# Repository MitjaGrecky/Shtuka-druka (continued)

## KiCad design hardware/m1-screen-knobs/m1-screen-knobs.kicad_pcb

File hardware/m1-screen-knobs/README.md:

# M1 - screen knobs module

**Current source (R148, 14.11.2026): rev 0.5** - four TI LP5864 (one per pair of rings), 12 RGB LEDs per ring, 4 corner holes + 3 in the gaps (x 56, 112, 168 mm, P97), 163 parts. `gen/design.py` builds rev 0.5 by default; `M1_LP=0` builds the old rev 0.3 (two IS31FL3741A, 13 LEDs, 8 holes), kept for history. The KiCad files here and `hardware/for-routing/M1` agree. The text below describes rev 0.1–0.3 (history).

Eight smooth encoders with push and touch (Param 1-8 under the screen), each with a ring of 13 RGB LEDs.
Spec and reasoning: `docs/ru/30_m1_screen_knobs.md`. History (rev 0.1): schematic done, board routed except 4 connections around U1; light guide (`mech/m1_light_guide.stl`) ready to print.

| | |
|---|---|
| Board | 224 x 34 mm, 4 layers; panel position x 108.75-332.75, y 263-297 (knob row y 277, panel fold y 300) |
| Top side | 8 x Alps EC11E (smooth, switch), 104 x XINGLIGHT XL-1615RGBC-RF (LCSC C965840) |
| Bottom side | IS31FL3741A LED driver (C2940604), CY8CMBR3108 touch (C462528), 3 x 74HC165, passives, J1 |
| Bus J1 | 2 x 7, 1.27 mm: +5V x2, +3V3, GND x4, SDA, SCL, INT, SR_LOAD, SR_CLK, SR_OUT, SR_IN |
| I2C | LED driver 0x30 (ADDR=GND, R3; 0x31-0x33 via R4-R6), touch 0x37 |
| LED matrix | LED n = 13 (ring-1) + (dot-1): SW = n mod 9 + 1, CS = 3 (n div 9) + 1..3 (R, G, B); CS37-39 unused |
| Shift chain | host reads U3 D7..D0, U4, U5: E1 A, E1 B, E1 push, E2 A, ... E8 push |

## Files

- `m1-screen-knobs.kicad_pro/.kicad_sch/.kicad_pcb` - open in KiCad 10 (written in the KiCad 7 format; KiCad 10 upgrades on save).
- `mech/m1_light_guide.stl` - the light guide (R126), black PETG/PLA, 0.2 mm layers.
- `lib/` - project symbols (IS31FL3741A, XL-1615RGBC-RF, encoder with touch pin) and footprints (LED 1615, QFN-60).
- `gen/` - the generators. Edit `design.py`, then run:

```
python3 gen/make_lib.py     # symbols and footprints
python3 gen/make_sch.py     # schematic
python3 gen/make_pcb.py     # board: placement, nets, GND planes (needs KiCad's pcbnew module)
python3 gen/make_pcb.py --route freerouting-1.9.0.jar --passes 16 --finish   # + autorouting (xvfb-run, Java)
python3 gen/make_pcb.py --ses gen/last_route.ses --finish                     # rebuild from the last routing
python3 gen/make_light_guide.py mech             # light guide STL (needs bpy)
```

`UNROUTED` marks the board as not routed yet: CI keeps the DRC report but does not fail.
`QUILTER.md` - rules for handing the board to an external layout service; the parts fixed by the panel are locked.

License: CERN-OHL-S-2.0 (hardware), AGPL-3.0-or-later (scripts).

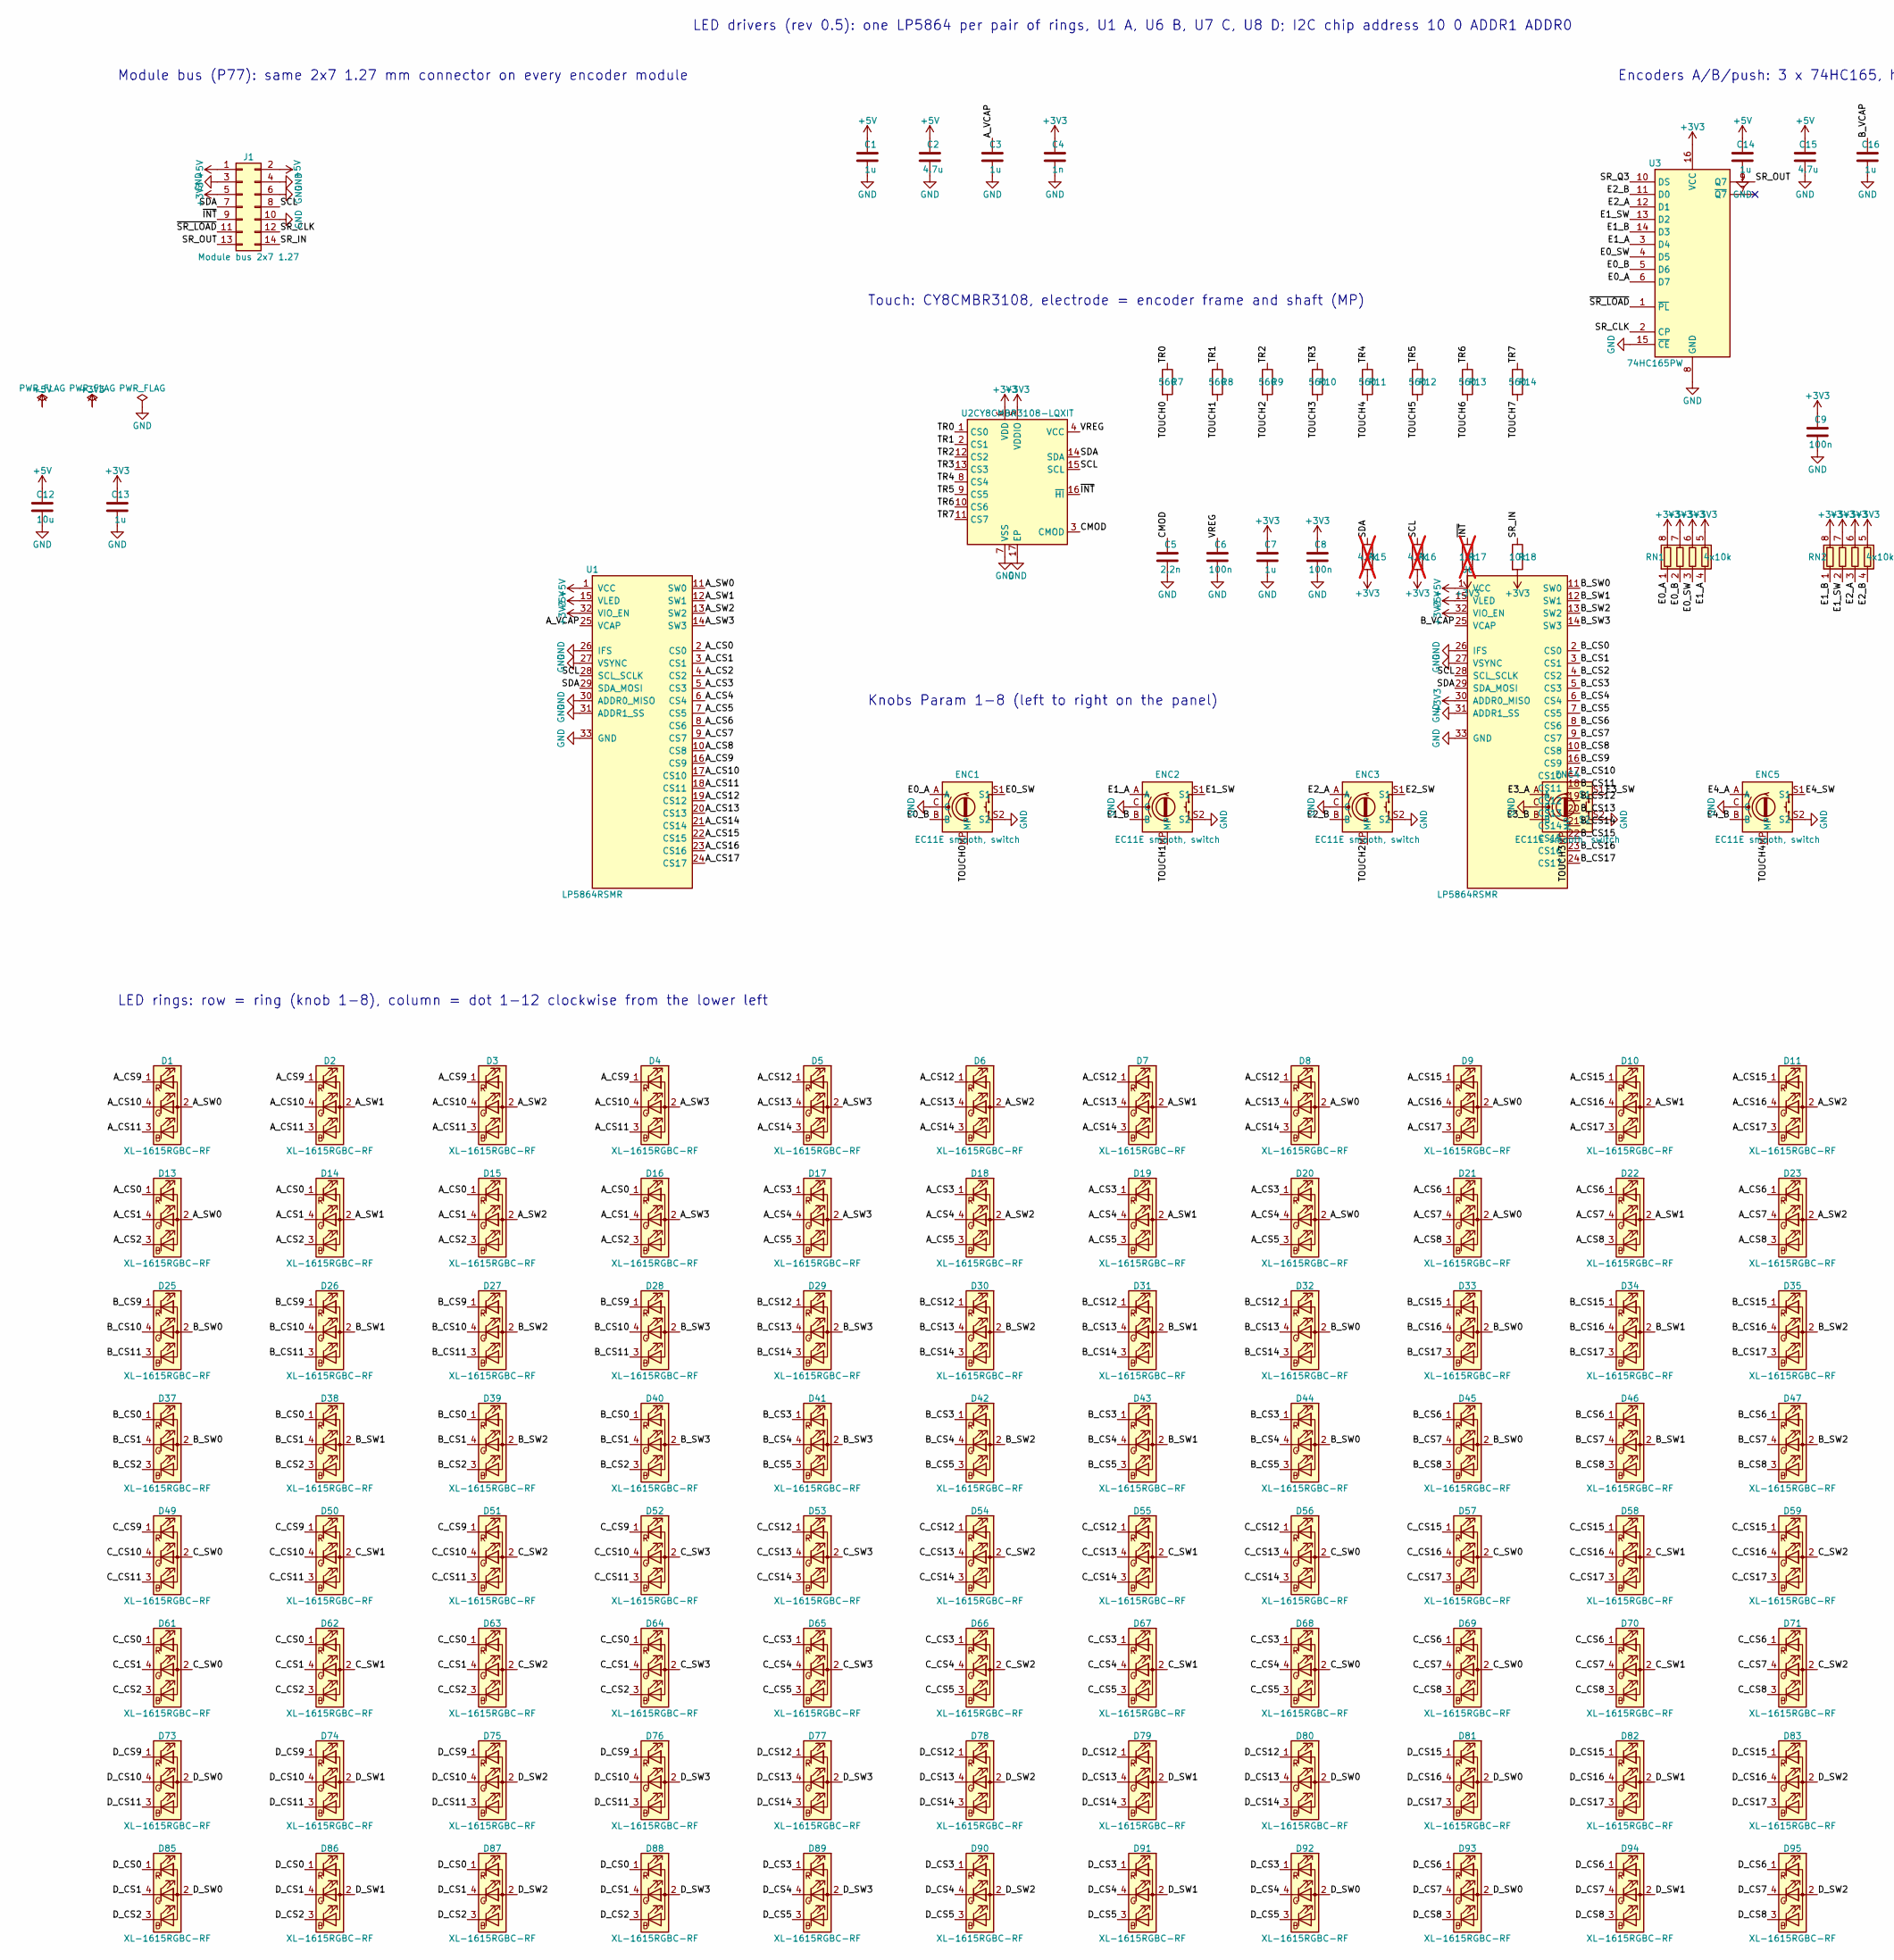
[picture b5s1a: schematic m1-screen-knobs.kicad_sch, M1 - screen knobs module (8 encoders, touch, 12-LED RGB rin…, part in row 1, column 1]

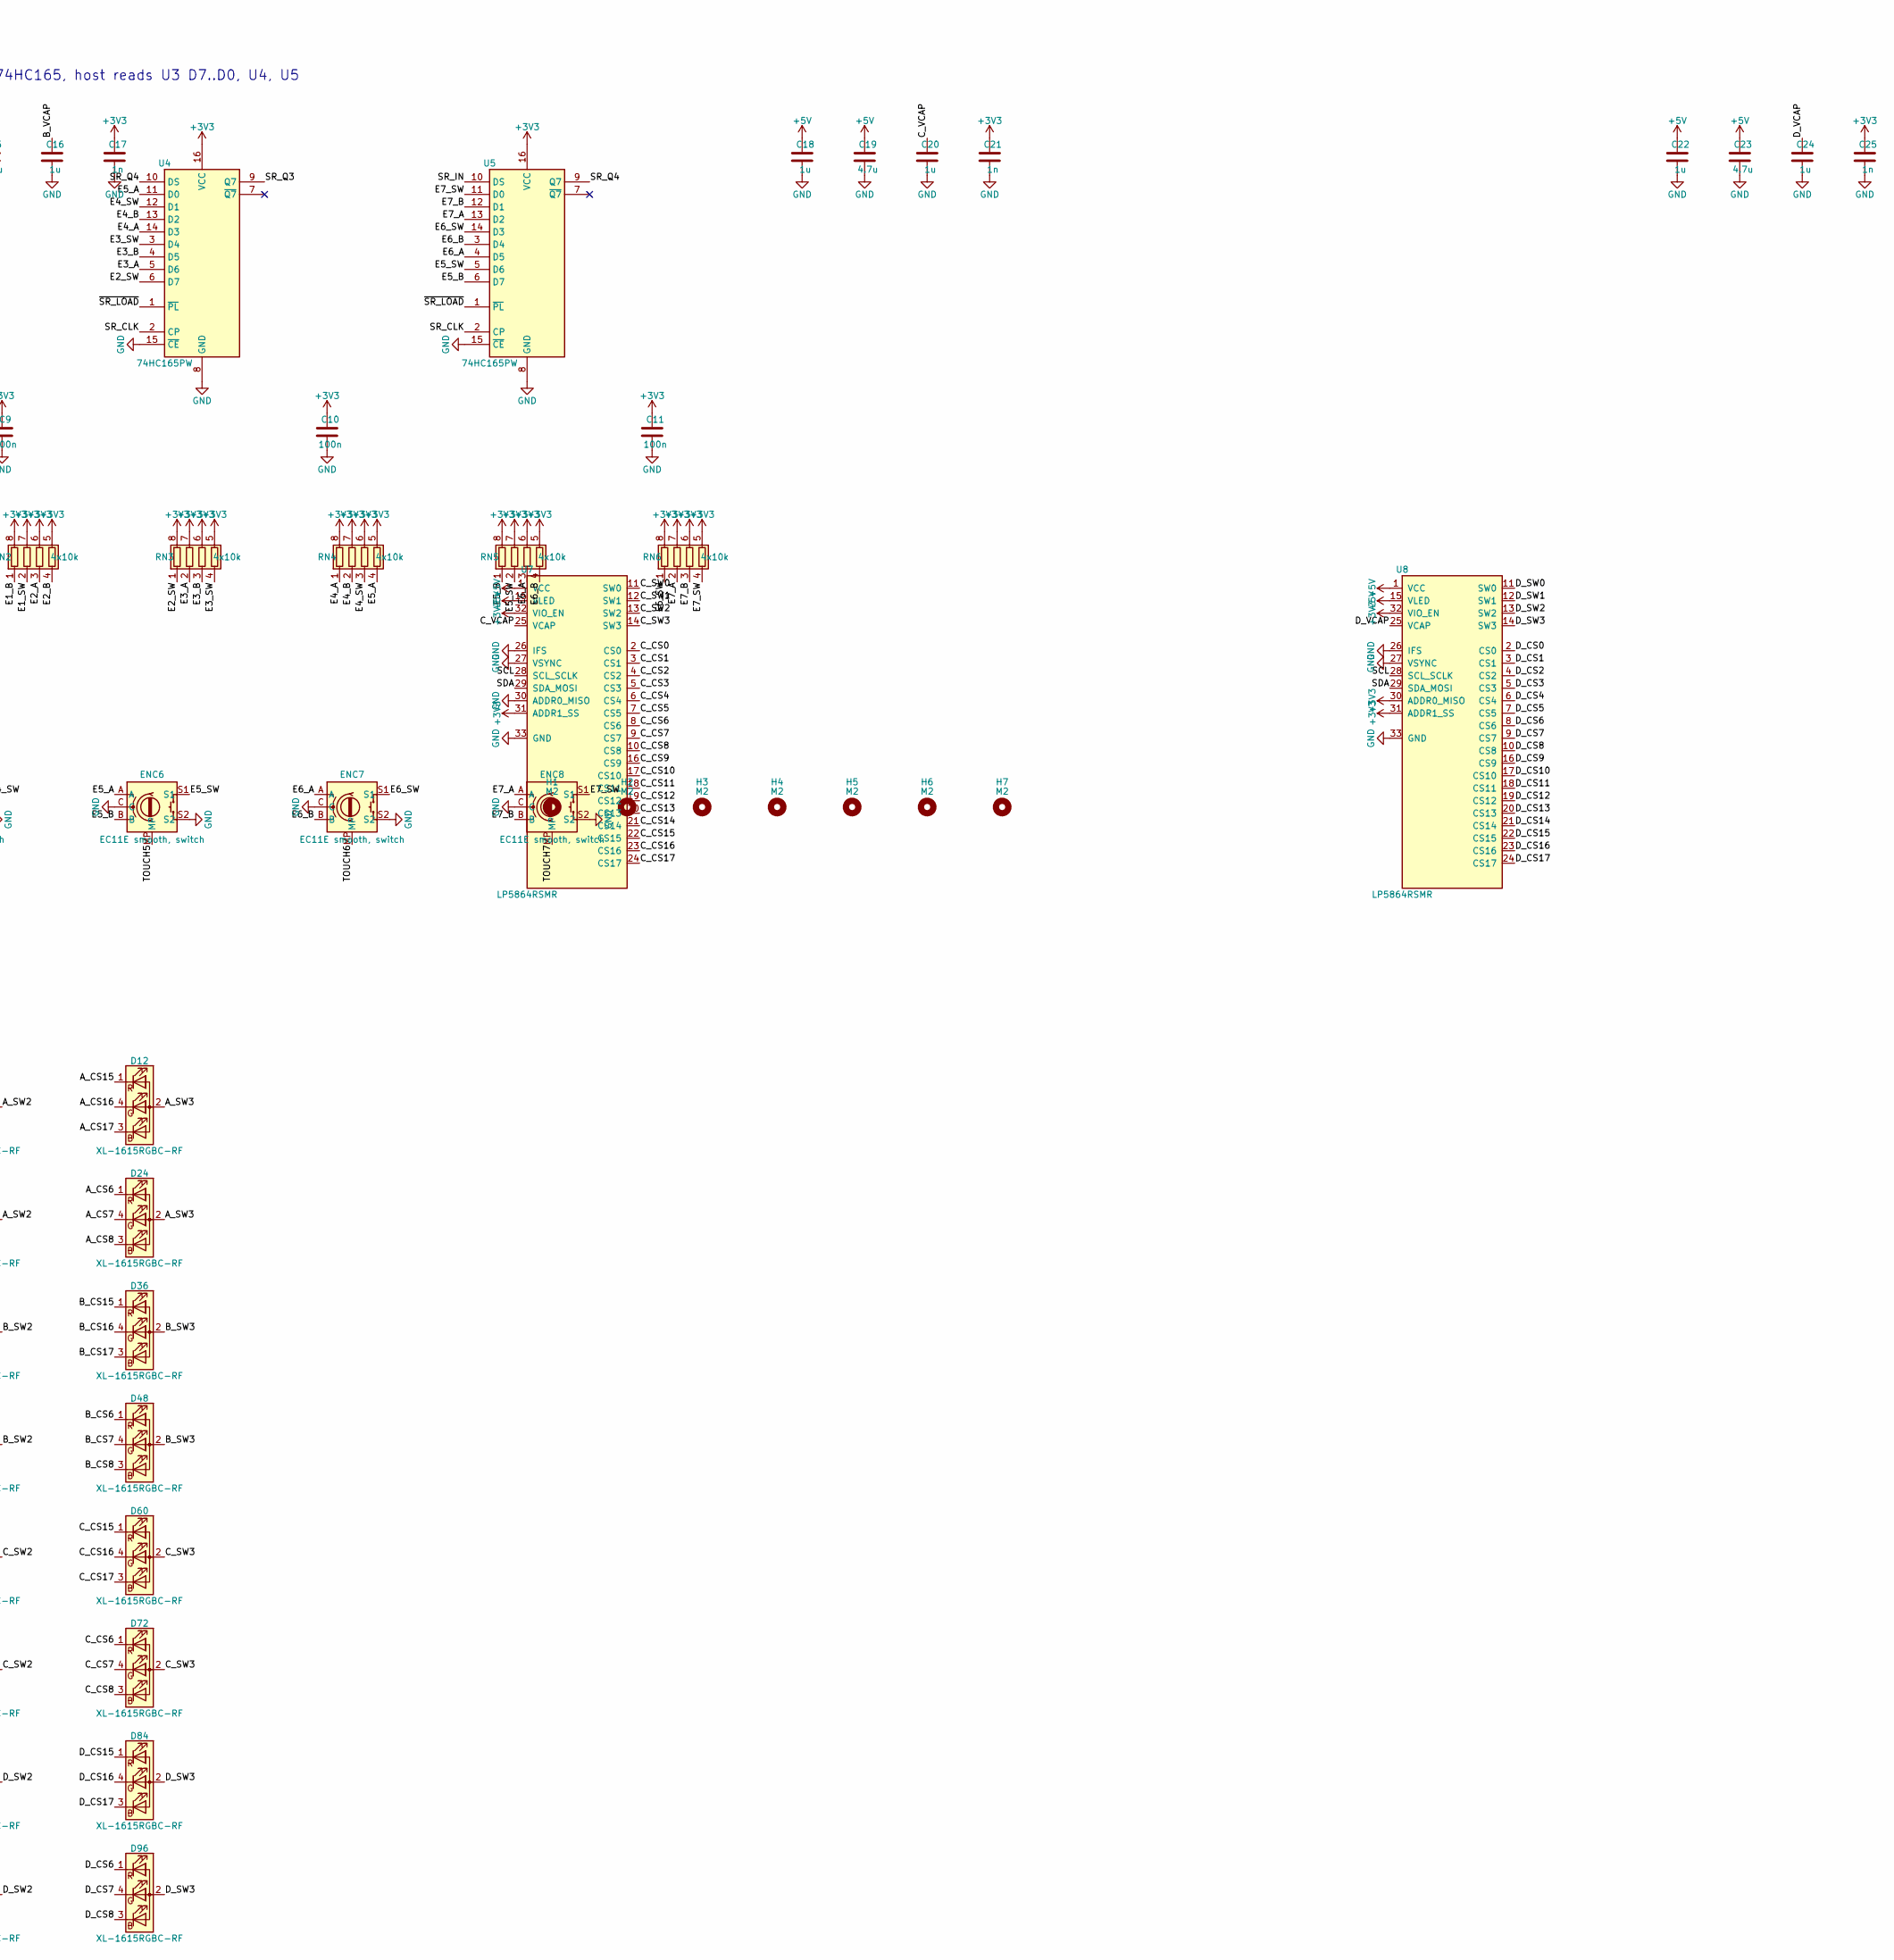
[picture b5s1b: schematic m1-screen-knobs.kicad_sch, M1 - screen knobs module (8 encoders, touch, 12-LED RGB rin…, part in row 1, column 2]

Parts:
C1, C3, C7, C13, C14, C16, C18, C20, C22, C24: 1u; C_0402_1005Metric
C2, C15, C19, C23: 4.7u; C_0805_2012Metric
C4, C17, C21, C25: 1n; C_0402_1005Metric
C5: 2.2n; C_0402_1005Metric
C6, C8, C9, C10, C11: 100n; C_0402_1005Metric
C12: 10u; C_0805_2012Metric
D1, D2, D3, D4, D5, D6, D7, D8, D9, D10, D11, D12, D13, D14, D15, D16, D17, D18, D19, D20, D21, D22, D23, D24, D25, D26, D27, D28, D29, D30, D31, D32, D33, D34, D35, D36, D37, D38, D39, D40, D41, D42, D43, D44, D45, D46, D47, D48, D49, D50, D51, D52, D53, D54, D55, D56, D57, D58, D59, D60, D61, D62, D63, D64, D65, D66, D67, D68, D69, D70, D71, D72, D73, D74, D75, D76, D77, D78, D79, D80, D81, D82, D83, D84, D85, D86, D87, D88, D89, D90, D91, D92, D93, D94, D95, D96: XL-1615RGBC-RF; LED_RGB_XL-1615RGBC_1.6x1.5mm; LCSC C965840
ENC1, ENC2, ENC3, ENC4, ENC5, ENC6, ENC7, ENC8: EC11E smooth, switch; RotaryEncoder_Alps_EC11E-Switch_Vertical_H20mm_Ring
H1, H2, H3, H4, H5, H6, H7: M2; MountingHole_2.2mm_M2
J1: Module bus 2x7 1.27; PinHeader_2x07_P1.27mm_Horizontal; LCSC C22438113
R7, R8, R9, R10, R11, R12, R13, R14: 560; R_0402_1005Metric
R15, R16: 4.7k; R_0402_1005Metric; not fitted
R17: 10k; R_0402_1005Metric; not fitted
R18: 10k; R_0402_1005Metric
RN1, RN2, RN3, RN4, RN5, RN6: 4x10k; R_Array_Convex_4x0402
U1, U6, U7, U8: LP5864RSMR; VQFN-32-1EP_4x4mm_P0.4mm_EP2.8x2.8mm; LCSC C5220564
U2: CY8CMBR3108-LQXIT; QFN-16-1EP_3x3mm_P0.5mm_EP1.7x1.7mm; LCSC C462528
U3, U4, U5: 74HC165PW; TSSOP-16_4.4x5mm_P0.65mm

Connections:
+3V3: C4.1, C7.1, C8.1, C9.1, C10.1, C11.1, C13.1, C17.1, C21.1, C25.1, J1.5, R15.2, R16.2, R17.2, R18.2, RN1.5 (R4.2), RN1.6 (R3.2), RN1.7 (R2.2), RN1.8 (R1.2), RN2.5 (R4.2), RN2.6 (R3.2), RN2.7 (R2.2), RN2.8 (R1.2), RN3.5 (R4.2), RN3.6 (R3.2), RN3.7 (R2.2), RN3.8 (R1.2), RN4.5 (R4.2), RN4.6 (R3.2), RN4.7 (R2.2), RN4.8 (R1.2), RN5.5 (R4.2), RN5.6 (R3.2), RN5.7 (R2.2), RN5.8 (R1.2), RN6.5 (R4.2), RN6.6 (R3.2), RN6.7 (R2.2), RN6.8 (R1.2), U1.32 (VIO_EN), U2.5 (VDDIO), U2.6 (VDD), U3.16 (VCC), U4.16 (VCC), U5.16 (VCC), U6.30 (ADDR0_MISO), U6.32 (VIO_EN), U7.31 (ADDR1_SS), U7.32 (VIO_EN), U8.30 (ADDR0_MISO), U8.31 (ADDR1_SS), U8.32 (VIO_EN)
+5V: C1.1, C2.1, C12.1, C14.1, C15.1, C18.1, C19.1, C22.1, C23.1, J1.1, J1.2, U1.1 (VCC), U1.15 (VLED), U6.1 (VCC), U6.15 (VLED), U7.1 (VCC), U7.15 (VLED), U8.1 (VCC), U8.15 (VLED)
/A_CS0: D13.1 (RK), D14.1 (RK), D15.1 (RK), D16.1 (RK), U1.2 (CS0)
/A_CS1: D13.4 (GK), D14.4 (GK), D15.4 (GK), D16.4 (GK), U1.3 (CS1)
/A_CS2: D13.3 (BK), D14.3 (BK), D15.3 (BK), D16.3 (BK), U1.4 (CS2)
/A_CS3: D17.1 (RK), D18.1 (RK), D19.1 (RK), D20.1 (RK), U1.5 (CS3)
/A_CS4: D17.4 (GK), D18.4 (GK), D19.4 (GK), D20.4 (GK), U1.6 (CS4)
/A_CS5: D17.3 (BK), D18.3 (BK), D19.3 (BK), D20.3 (BK), U1.7 (CS5)
/A_CS6: D21.1 (RK), D22.1 (RK), D23.1 (RK), D24.1 (RK), U1.8 (CS6)
/A_CS7: D21.4 (GK), D22.4 (GK), D23.4 (GK), D24.4 (GK), U1.9 (CS7)
/A_CS8: D21.3 (BK), D22.3 (BK), D23.3 (BK), D24.3 (BK), U1.10 (CS8)
/A_CS9: D1.1 (RK), D2.1 (RK), D3.1 (RK), D4.1 (RK), U1.16 (CS9)
/A_CS10: D1.4 (GK), D2.4 (GK), D3.4 (GK), D4.4 (GK), U1.17 (CS10)
/A_CS11: D1.3 (BK), D2.3 (BK), D3.3 (BK), D4.3 (BK), U1.18 (CS11)
/A_CS12: D5.1 (RK), D6.1 (RK), D7.1 (RK), D8.1 (RK), U1.19 (CS12)
/A_CS13: D5.4 (GK), D6.4 (GK), D7.4 (GK), D8.4 (GK), U1.20 (CS13)
/A_CS14: D5.3 (BK), D6.3 (BK), D7.3 (BK), D8.3 (BK), U1.21 (CS14)
/A_CS15: D9.1 (RK), D10.1 (RK), D11.1 (RK), D12.1 (RK), U1.22 (CS15)
/A_CS16: D9.4 (GK), D10.4 (GK), D11.4 (GK), D12.4 (GK), U1.23 (CS16)
/A_CS17: D9.3 (BK), D10.3 (BK), D11.3 (BK), D12.3 (BK), U1.24 (CS17)
/A_SW0: D1.2 (A), D8.2 (A), D9.2 (A), D13.2 (A), D20.2 (A), D21.2 (A), U1.11 (SW0)
/A_SW1: D2.2 (A), D7.2 (A), D10.2 (A), D14.2 (A), D19.2 (A), D22.2 (A), U1.12 (SW1)
/A_SW2: D3.2 (A), D6.2 (A), D11.2 (A), D15.2 (A), D18.2 (A), D23.2 (A), U1.13 (SW2)
/A_SW3: D4.2 (A), D5.2 (A), D12.2 (A), D16.2 (A), D17.2 (A), D24.2 (A), U1.14 (SW3)
/A_VCAP: C3.1, U1.25 (VCAP)
/B_CS0: D37.1 (RK), D38.1 (RK), D39.1 (RK), D40.1 (RK), U6.2 (CS0)
/B_CS1: D37.4 (GK), D38.4 (GK), D39.4 (GK), D40.4 (GK), U6.3 (CS1)
/B_CS2: D37.3 (BK), D38.3 (BK), D39.3 (BK), D40.3 (BK), U6.4 (CS2)
/B_CS3: D41.1 (RK), D42.1 (RK), D43.1 (RK), D44.1 (RK), U6.5 (CS3)
/B_CS4: D41.4 (GK), D42.4 (GK), D43.4 (GK), D44.4 (GK), U6.6 (CS4)
/B_CS5: D41.3 (BK), D42.3 (BK), D43.3 (BK), D44.3 (BK), U6.7 (CS5)
/B_CS6: D45.1 (RK), D46.1 (RK), D47.1 (RK), D48.1 (RK), U6.8 (CS6)
/B_CS7: D45.4 (GK), D46.4 (GK), D47.4 (GK), D48.4 (GK), U6.9 (CS7)
/B_CS8: D45.3 (BK), D46.3 (BK), D47.3 (BK), D48.3 (BK), U6.10 (CS8)
/B_CS9: D25.1 (RK), D26.1 (RK), D27.1 (RK), D28.1 (RK), U6.16 (CS9)
/B_CS10: D25.4 (GK), D26.4 (GK), D27.4 (GK), D28.4 (GK), U6.17 (CS10)
/B_CS11: D25.3 (BK), D26.3 (BK), D27.3 (BK), D28.3 (BK), U6.18 (CS11)
/B_CS12: D29.1 (RK), D30.1 (RK), D31.1 (RK), D32.1 (RK), U6.19 (CS12)
/B_CS13: D29.4 (GK), D30.4 (GK), D31.4 (GK), D32.4 (GK), U6.20 (CS13)
/B_CS14: D29.3 (BK), D30.3 (BK), D31.3 (BK), D32.3 (BK), U6.21 (CS14)
/B_CS15: D33.1 (RK), D34.1 (RK), D35.1 (RK), D36.1 (RK), U6.22 (CS15)
/B_CS16: D33.4 (GK), D34.4 (GK), D35.4 (GK), D36.4 (GK), U6.23 (CS16)
/B_CS17: D33.3 (BK), D34.3 (BK), D35.3 (BK), D36.3 (BK), U6.24 (CS17)
/B_SW0: D25.2 (A), D32.2 (A), D33.2 (A), D37.2 (A), D44.2 (A), D45.2 (A), U6.11 (SW0)
/B_SW1: D26.2 (A), D31.2 (A), D34.2 (A), D38.2 (A), D43.2 (A), D46.2 (A), U6.12 (SW1)
/B_SW2: D27.2 (A), D30.2 (A), D35.2 (A), D39.2 (A), D42.2 (A), D47.2 (A), U6.13 (SW2)
/B_SW3: D28.2 (A), D29.2 (A), D36.2 (A), D40.2 (A), D41.2 (A), D48.2 (A), U6.14 (SW3)
/B_VCAP: C16.1, U6.25 (VCAP)
/CMOD: C5.1, U2.3 (CMOD)
/C_CS0: D61.1 (RK), D62.1 (RK), D63.1 (RK), D64.1 (RK), U7.2 (CS0)
/C_CS1: D61.4 (GK), D62.4 (GK), D63.4 (GK), D64.4 (GK), U7.3 (CS1)
/C_CS2: D61.3 (BK), D62.3 (BK), D63.3 (BK), D64.3 (BK), U7.4 (CS2)
/C_CS3: D65.1 (RK), D66.1 (RK), D67.1 (RK), D68.1 (RK), U7.5 (CS3)
/C_CS4: D65.4 (GK), D66.4 (GK), D67.4 (GK), D68.4 (GK), U7.6 (CS4)
/C_CS5: D65.3 (BK), D66.3 (BK), D67.3 (BK), D68.3 (BK), U7.7 (CS5)
/C_CS6: D69.1 (RK), D70.1 (RK), D71.1 (RK), D72.1 (RK), U7.8 (CS6)
/C_CS7: D69.4 (GK), D70.4 (GK), D71.4 (GK), D72.4 (GK), U7.9 (CS7)
/C_CS8: D69.3 (BK), D70.3 (BK), D71.3 (BK), D72.3 (BK), U7.10 (CS8)
/C_CS9: D49.1 (RK), D50.1 (RK), D51.1 (RK), D52.1 (RK), U7.16 (CS9)
/C_CS10: D49.4 (GK), D50.4 (GK), D51.4 (GK), D52.4 (GK), U7.17 (CS10)
/C_CS11: D49.3 (BK), D50.3 (BK), D51.3 (BK), D52.3 (BK), U7.18 (CS11)
/C_CS12: D53.1 (RK), D54.1 (RK), D55.1 (RK), D56.1 (RK), U7.19 (CS12)
/C_CS13: D53.4 (GK), D54.4 (GK), D55.4 (GK), D56.4 (GK), U7.20 (CS13)
/C_CS14: D53.3 (BK), D54.3 (BK), D55.3 (BK), D56.3 (BK), U7.21 (CS14)
/C_CS15: D57.1 (RK), D58.1 (RK), D59.1 (RK), D60.1 (RK), U7.22 (CS15)
/C_CS16: D57.4 (GK), D58.4 (GK), D59.4 (GK), D60.4 (GK), U7.23 (CS16)
/C_CS17: D57.3 (BK), D58.3 (BK), D59.3 (BK), D60.3 (BK), U7.24 (CS17)
/C_SW0: D49.2 (A), D56.2 (A), D57.2 (A), D61.2 (A), D68.2 (A), D69.2 (A), U7.11 (SW0)
/C_SW1: D50.2 (A), D55.2 (A), D58.2 (A), D62.2 (A), D67.2 (A), D70.2 (A), U7.12 (SW1)
/C_SW2: D51.2 (A), D54.2 (A), D59.2 (A), D63.2 (A), D66.2 (A), D71.2 (A), U7.13 (SW2)
/C_SW3: D52.2 (A), D53.2 (A), D60.2 (A), D64.2 (A), D65.2 (A), D72.2 (A), U7.14 (SW3)
/C_VCAP: C20.1, U7.25 (VCAP)
/D_CS0: D85.1 (RK), D86.1 (RK), D87.1 (RK), D88.1 (RK), U8.2 (CS0)
/D_CS1: D85.4 (GK), D86.4 (GK), D87.4 (GK), D88.4 (GK), U8.3 (CS1)
/D_CS2: D85.3 (BK), D86.3 (BK), D87.3 (BK), D88.3 (BK), U8.4 (CS2)
/D_CS3: D89.1 (RK), D90.1 (RK), D91.1 (RK), D92.1 (RK), U8.5 (CS3)
/D_CS4: D89.4 (GK), D90.4 (GK), D91.4 (GK), D92.4 (GK), U8.6 (CS4)
/D_CS5: D89.3 (BK), D90.3 (BK), D91.3 (BK), D92.3 (BK), U8.7 (CS5)
/D_CS6: D93.1 (RK), D94.1 (RK), D95.1 (RK), D96.1 (RK), U8.8 (CS6)
/D_CS7: D93.4 (GK), D94.4 (GK), D95.4 (GK), D96.4 (GK), U8.9 (CS7)
/D_CS8: D93.3 (BK), D94.3 (BK), D95.3 (BK), D96.3 (BK), U8.10 (CS8)
/D_CS9: D73.1 (RK), D74.1 (RK), D75.1 (RK), D76.1 (RK), U8.16 (CS9)
/D_CS10: D73.4 (GK), D74.4 (GK), D75.4 (GK), D76.4 (GK), U8.17 (CS10)
/D_CS11: D73.3 (BK), D74.3 (BK), D75.3 (BK), D76.3 (BK), U8.18 (CS11)
/D_CS12: D77.1 (RK), D78.1 (RK), D79.1 (RK), D80.1 (RK), U8.19 (CS12)
/D_CS13: D77.4 (GK), D78.4 (GK), D79.4 (GK), D80.4 (GK), U8.20 (CS13)
/D_CS14: D77.3 (BK), D78.3 (BK), D79.3 (BK), D80.3 (BK), U8.21 (CS14)
/D_CS15: D81.1 (RK), D82.1 (RK), D83.1 (RK), D84.1 (RK), U8.22 (CS15)
/D_CS16: D81.4 (GK), D82.4 (GK), D83.4 (GK), D84.4 (GK), U8.23 (CS16)
/D_CS17: D81.3 (BK), D82.3 (BK), D83.3 (BK), D84.3 (BK), U8.24 (CS17)
/D_SW0: D73.2 (A), D80.2 (A), D81.2 (A), D85.2 (A), D92.2 (A), D93.2 (A), U8.11 (SW0)
/D_SW1: D74.2 (A), D79.2 (A), D82.2 (A), D86.2 (A), D91.2 (A), D94.2 (A), U8.12 (SW1)
/D_SW2: D75.2 (A), D78.2 (A), D83.2 (A), D87.2 (A), D90.2 (A), D95.2 (A), U8.13 (SW2)
/D_SW3: D76.2 (A), D77.2 (A), D84.2 (A), D88.2 (A), D89.2 (A), D96.2 (A), U8.14 (SW3)
/D_VCAP: C24.1, U8.25 (VCAP)
/E0_A: ENC1.A, RN1.1 (R1.1), U3.6 (D7)
/E0_B: ENC1.B, RN1.2 (R2.1), U3.5 (D6)
/E0_SW: ENC1.S1, RN1.3 (R3.1), U3.4 (D5)
/E1_A: ENC2.A, RN1.4 (R4.1), U3.3 (D4)
/E1_B: ENC2.B, RN2.1 (R1.1), U3.14 (D3)
/E1_SW: ENC2.S1, RN2.2 (R2.1), U3.13 (D2)
/E2_A: ENC3.A, RN2.3 (R3.1), U3.12 (D1)
/E2_B: ENC3.B, RN2.4 (R4.1), U3.11 (D0)
/E2_SW: ENC3.S1, RN3.1 (R1.1), U4.6 (D7)
/E3_A: ENC4.A, RN3.2 (R2.1), U4.5 (D6)
/E3_B: ENC4.B, RN3.3 (R3.1), U4.4 (D5)
/E3_SW: ENC4.S1, RN3.4 (R4.1), U4.3 (D4)
/E4_A: ENC5.A, RN4.1 (R1.1), U4.14 (D3)
/E4_B: ENC5.B, RN4.2 (R2.1), U4.13 (D2)
/E4_SW: ENC5.S1, RN4.3 (R3.1), U4.12 (D1)
/E5_A: ENC6.A, RN4.4 (R4.1), U4.11 (D0)
/E5_B: ENC6.B, RN5.1 (R1.1), U5.6 (D7)
/E5_SW: ENC6.S1, RN5.2 (R2.1), U5.5 (D6)
/E6_A: ENC7.A, RN5.3 (R3.1), U5.4 (D5)
/E6_B: ENC7.B, RN5.4 (R4.1), U5.3 (D4)
/E6_SW: ENC7.S1, RN6.1 (R1.1), U5.14 (D3)
/E7_A: ENC8.A, RN6.2 (R2.1), U5.13 (D2)
/E7_B: ENC8.B, RN6.3 (R3.1), U5.12 (D1)
/E7_SW: ENC8.S1, RN6.4 (R4.1), U5.11 (D0)
/SCL: J1.8, R16.1, U1.28 (SCL_SCLK), U2.15 (SCL), U6.28 (SCL_SCLK), U7.28 (SCL_SCLK), U8.28 (SCL_SCLK)
/SDA: J1.7, R15.1, U1.29 (SDA_MOSI), U2.14 (SDA), U6.29 (SDA_MOSI), U7.29 (SDA_MOSI), U8.29 (SDA_MOSI)
/SR_CLK: J1.12, U3.2 (CP), U4.2 (CP), U5.2 (CP)
/SR_IN: J1.14, R18.1, U5.10 (DS)
/SR_OUT: J1.13, U3.9 (Q7)
/SR_Q3: U3.10 (DS), U4.9 (Q7)
/SR_Q4: U4.10 (DS), U5.9 (Q7)
/TOUCH0: ENC1.MP, R7.2
/TOUCH1: ENC2.MP, R8.2
/TOUCH2: ENC3.MP, R9.2
/TOUCH3: ENC4.MP, R10.2
/TOUCH4: ENC5.MP, R11.2
/TOUCH5: ENC6.MP, R12.2
/TOUCH6: ENC7.MP, R13.2
/TOUCH7: ENC8.MP, R14.2
/TR0: R7.1, U2.1 (CS0)
/TR1: R8.1, U2.2 (CS1)
/TR2: R9.1, U2.12 (CS2)
/TR3: R10.1, U2.13 (CS3)
/TR4: R11.1, U2.8 (CS4)
/TR5: R12.1, U2.9 (CS5)
/TR6: R13.1, U2.10 (CS6)
/TR7: R14.1, U2.11 (CS7)
/VREG: C6.1, U2.4 (VCC)
/~INT: J1.9, R17.1, U2.16 (~HI)
/~SR_LOAD: J1.11, U3.1 (~PL), U4.1 (~PL), U5.1 (~PL)
GND: C1.2, C2.2, C3.2, C4.2, C5.2, C6.2, C7.2, C8.2, C9.2, C10.2, C11.2, C12.2, C13.2, C14.2, C15.2, C16.2, C17.2, C18.2, C19.2, C20.2, C21.2, C22.2, C23.2, C24.2, C25.2, ENC1.C, ENC1.S2, ENC2.C, ENC2.S2, ENC3.C, ENC3.S2, ENC4.C, ENC4.S2, ENC5.C, ENC5.S2, ENC6.C, ENC6.S2, ENC7.C, ENC7.S2, ENC8.C, ENC8.S2, J1.3, J1.4, J1.6, J1.10, U1.26 (IFS), U1.27 (VSYNC), U1.30 (ADDR0_MISO), U1.31 (ADDR1_SS), U1.33 (GND), U2.7 (VSS), U2.17 (EP), U3.8 (GND), U3.15 (~CE), U4.8 (GND), U4.15 (~CE), U5.8 (GND), U5.15 (~CE), U6.26 (IFS), U6.27 (VSYNC), U6.31 (ADDR1_SS), U6.33 (GND), U7.26 (IFS), U7.27 (VSYNC), U7.30 (ADDR0_MISO), U7.33 (GND), U8.26 (IFS), U8.27 (VSYNC), U8.33 (GND)

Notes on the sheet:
Module bus (P77): same 2x7 1.27 mm connector on every encoder module
LED drivers (rev 0.5): one LP5864 per pair of rings, U1 A, U6 B, U7 C, U8 D; I2C chip address 10 0 ADDR1 ADDR0
Touch: CY8CMBR3108, electrode = encoder frame and shaft (MP)
Encoders A/B/push: 3 x 74HC165, host reads U3 D7..D0, U4, U5
Knobs Param 1-8 (left to right on the panel)
LED rings: row = ring (knob 1-8), column = dot 1-12 clockwise from the lower left

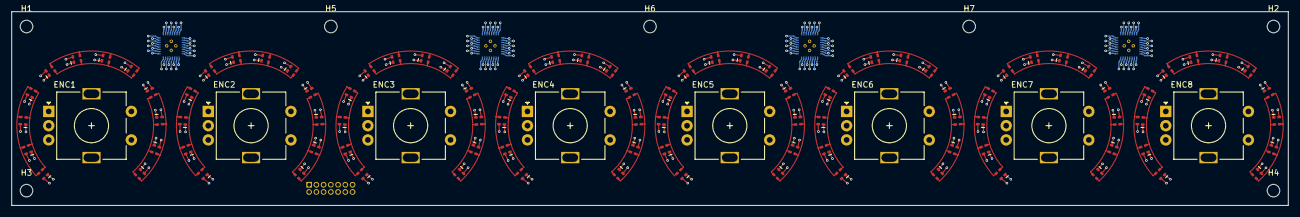
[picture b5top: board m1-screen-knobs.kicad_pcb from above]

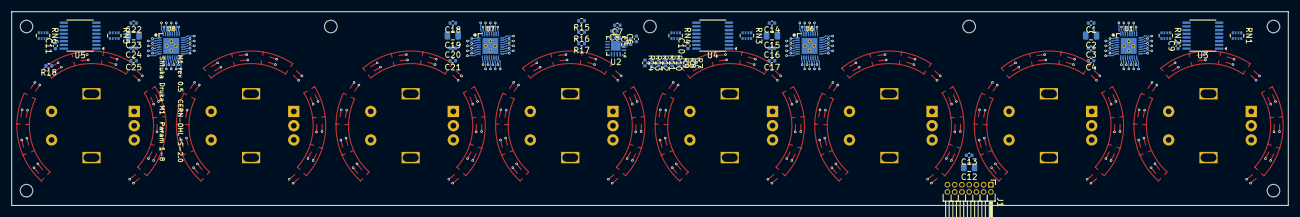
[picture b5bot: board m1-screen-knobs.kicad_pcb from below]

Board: 4 copper layers, 224.0 x 34.0 mm, 163 parts (52 on the bottom side), 146 nets.

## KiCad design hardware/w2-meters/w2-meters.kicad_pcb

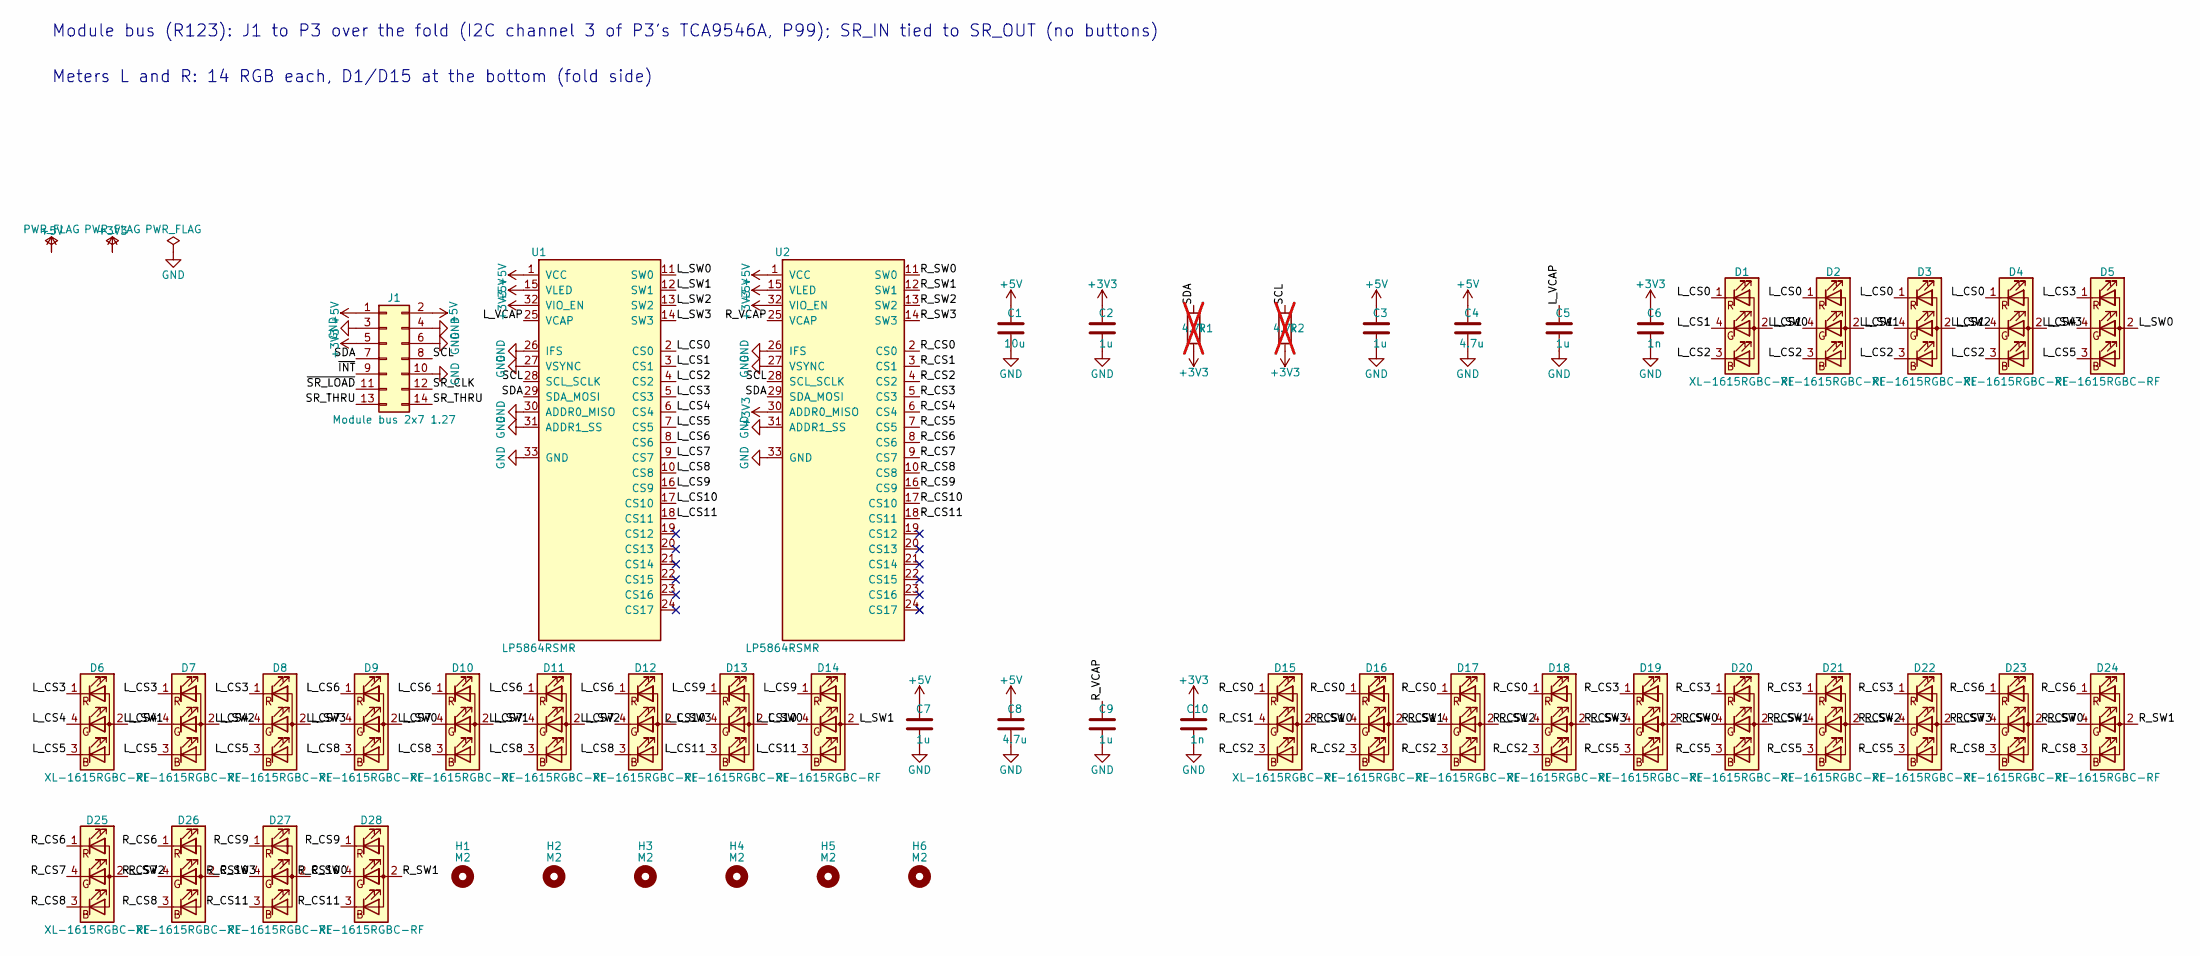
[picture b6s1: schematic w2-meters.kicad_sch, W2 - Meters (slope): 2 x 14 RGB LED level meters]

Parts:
C1: 10u; C_0805_2012Metric; LCSC C15850
C2, C3, C5, C7, C9: 1u; C_0402_1005Metric; LCSC C52923
C4, C8: 4.7u; C_0805_2012Metric; LCSC C1779
C6, C10: 1n; C_0402_1005Metric; LCSC C1523
D1, D2, D3, D4, D5, D6, D7, D8, D9, D10, D11, D12, D13, D14, D15, D16, D17, D18, D19, D20, D21, D22, D23, D24, D25, D26, D27, D28: XL-1615RGBC-RF; LED_RGB_XL-1615RGBC_1.6x1.5mm; LCSC C965840
H1, H2, H3, H4, H5, H6: M2; MountingHole_2.2mm_M2
J1: Module bus 2x7 1.27; PinHeader_2x07_P1.27mm_Vertical; LCSC C5372811
R1, R2: 4.7k; R_0402_1005Metric; LCSC C25900; not fitted
U1, U2: LP5864RSMR; VQFN-32-1EP_4x4mm_P0.4mm_EP2.8x2.8mm; LCSC C5220564

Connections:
+3V3: C2.1, C6.1, C10.1, J1.5, R1.2, R2.2, U1.32 (VIO_EN), U2.30 (ADDR0_MISO), U2.32 (VIO_EN)
+5V: C1.1, C3.1, C4.1, C7.1, C8.1, J1.1, J1.2, U1.1 (VCC), U1.15 (VLED), U2.1 (VCC), U2.15 (VLED)
/L_CS0: D1.1 (RK), D2.1 (RK), D3.1 (RK), D4.1 (RK), U1.2 (CS0)
/L_CS1: D1.4 (GK), D2.4 (GK), D3.4 (GK), D4.4 (GK), U1.3 (CS1)
/L_CS2: D1.3 (BK), D2.3 (BK), D3.3 (BK), D4.3 (BK), U1.4 (CS2)
/L_CS3: D5.1 (RK), D6.1 (RK), D7.1 (RK), D8.1 (RK), U1.5 (CS3)
/L_CS4: D5.4 (GK), D6.4 (GK), D7.4 (GK), D8.4 (GK), U1.6 (CS4)
/L_CS5: D5.3 (BK), D6.3 (BK), D7.3 (BK), D8.3 (BK), U1.7 (CS5)
/L_CS6: D9.1 (RK), D10.1 (RK), D11.1 (RK), D12.1 (RK), U1.8 (CS6)
/L_CS7: D9.4 (GK), D10.4 (GK), D11.4 (GK), D12.4 (GK), U1.9 (CS7)
/L_CS8: D9.3 (BK), D10.3 (BK), D11.3 (BK), D12.3 (BK), U1.10 (CS8)
/L_CS9: D13.1 (RK), D14.1 (RK), U1.16 (CS9)
/L_CS10: D13.4 (GK), D14.4 (GK), U1.17 (CS10)
/L_CS11: D13.3 (BK), D14.3 (BK), U1.18 (CS11)
/L_SW0: D1.2 (A), D5.2 (A), D9.2 (A), D13.2 (A), U1.11 (SW0)
/L_SW1: D2.2 (A), D6.2 (A), D10.2 (A), D14.2 (A), U1.12 (SW1)
/L_SW2: D3.2 (A), D7.2 (A), D11.2 (A), U1.13 (SW2)
/L_SW3: D4.2 (A), D8.2 (A), D12.2 (A), U1.14 (SW3)
/L_VCAP: C5.1, U1.25 (VCAP)
/R_CS0: D15.1 (RK), D16.1 (RK), D17.1 (RK), D18.1 (RK), U2.2 (CS0)
/R_CS1: D15.4 (GK), D16.4 (GK), D17.4 (GK), D18.4 (GK), U2.3 (CS1)
/R_CS2: D15.3 (BK), D16.3 (BK), D17.3 (BK), D18.3 (BK), U2.4 (CS2)
/R_CS3: D19.1 (RK), D20.1 (RK), D21.1 (RK), D22.1 (RK), U2.5 (CS3)
/R_CS4: D19.4 (GK), D20.4 (GK), D21.4 (GK), D22.4 (GK), U2.6 (CS4)
/R_CS5: D19.3 (BK), D20.3 (BK), D21.3 (BK), D22.3 (BK), U2.7 (CS5)
/R_CS6: D23.1 (RK), D24.1 (RK), D25.1 (RK), D26.1 (RK), U2.8 (CS6)
/R_CS7: D23.4 (GK), D24.4 (GK), D25.4 (GK), D26.4 (GK), U2.9 (CS7)
/R_CS8: D23.3 (BK), D24.3 (BK), D25.3 (BK), D26.3 (BK), U2.10 (CS8)
/R_CS9: D27.1 (RK), D28.1 (RK), U2.16 (CS9)
/R_CS10: D27.4 (GK), D28.4 (GK), U2.17 (CS10)
/R_CS11: D27.3 (BK), D28.3 (BK), U2.18 (CS11)
/R_SW0: D15.2 (A), D19.2 (A), D23.2 (A), D27.2 (A), U2.11 (SW0)
/R_SW1: D16.2 (A), D20.2 (A), D24.2 (A), D28.2 (A), U2.12 (SW1)
/R_SW2: D17.2 (A), D21.2 (A), D25.2 (A), U2.13 (SW2)
/R_SW3: D18.2 (A), D22.2 (A), D26.2 (A), U2.14 (SW3)
/R_VCAP: C9.1, U2.25 (VCAP)
/SCL: J1.8, R2.1, U1.28 (SCL_SCLK), U2.28 (SCL_SCLK)
/SDA: J1.7, R1.1, U1.29 (SDA_MOSI), U2.29 (SDA_MOSI)
/SR_CLK: J1.12
/SR_THRU: J1.13, J1.14
/~INT: J1.9
/~SR_LOAD: J1.11
GND: C1.2, C2.2, C3.2, C4.2, C5.2, C6.2, C7.2, C8.2, C9.2, C10.2, J1.3, J1.4, J1.6, J1.10, U1.26 (IFS), U1.27 (VSYNC), U1.30 (ADDR0_MISO), U1.31 (ADDR1_SS), U1.33 (GND), U2.26 (IFS), U2.27 (VSYNC), U2.31 (ADDR1_SS), U2.33 (GND)

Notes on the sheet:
Module bus (R123): J1 to P3 over the fold (I2C channel 3 of P3's TCA9546A, P99); SR_IN tied to SR_OUT (no buttons)
Meters L and R: 14 RGB each, D1/D15 at the bottom (fold side)

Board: 2 copper layers, 49 parts (15 on the bottom side), 40 nets, no tracks yet.
